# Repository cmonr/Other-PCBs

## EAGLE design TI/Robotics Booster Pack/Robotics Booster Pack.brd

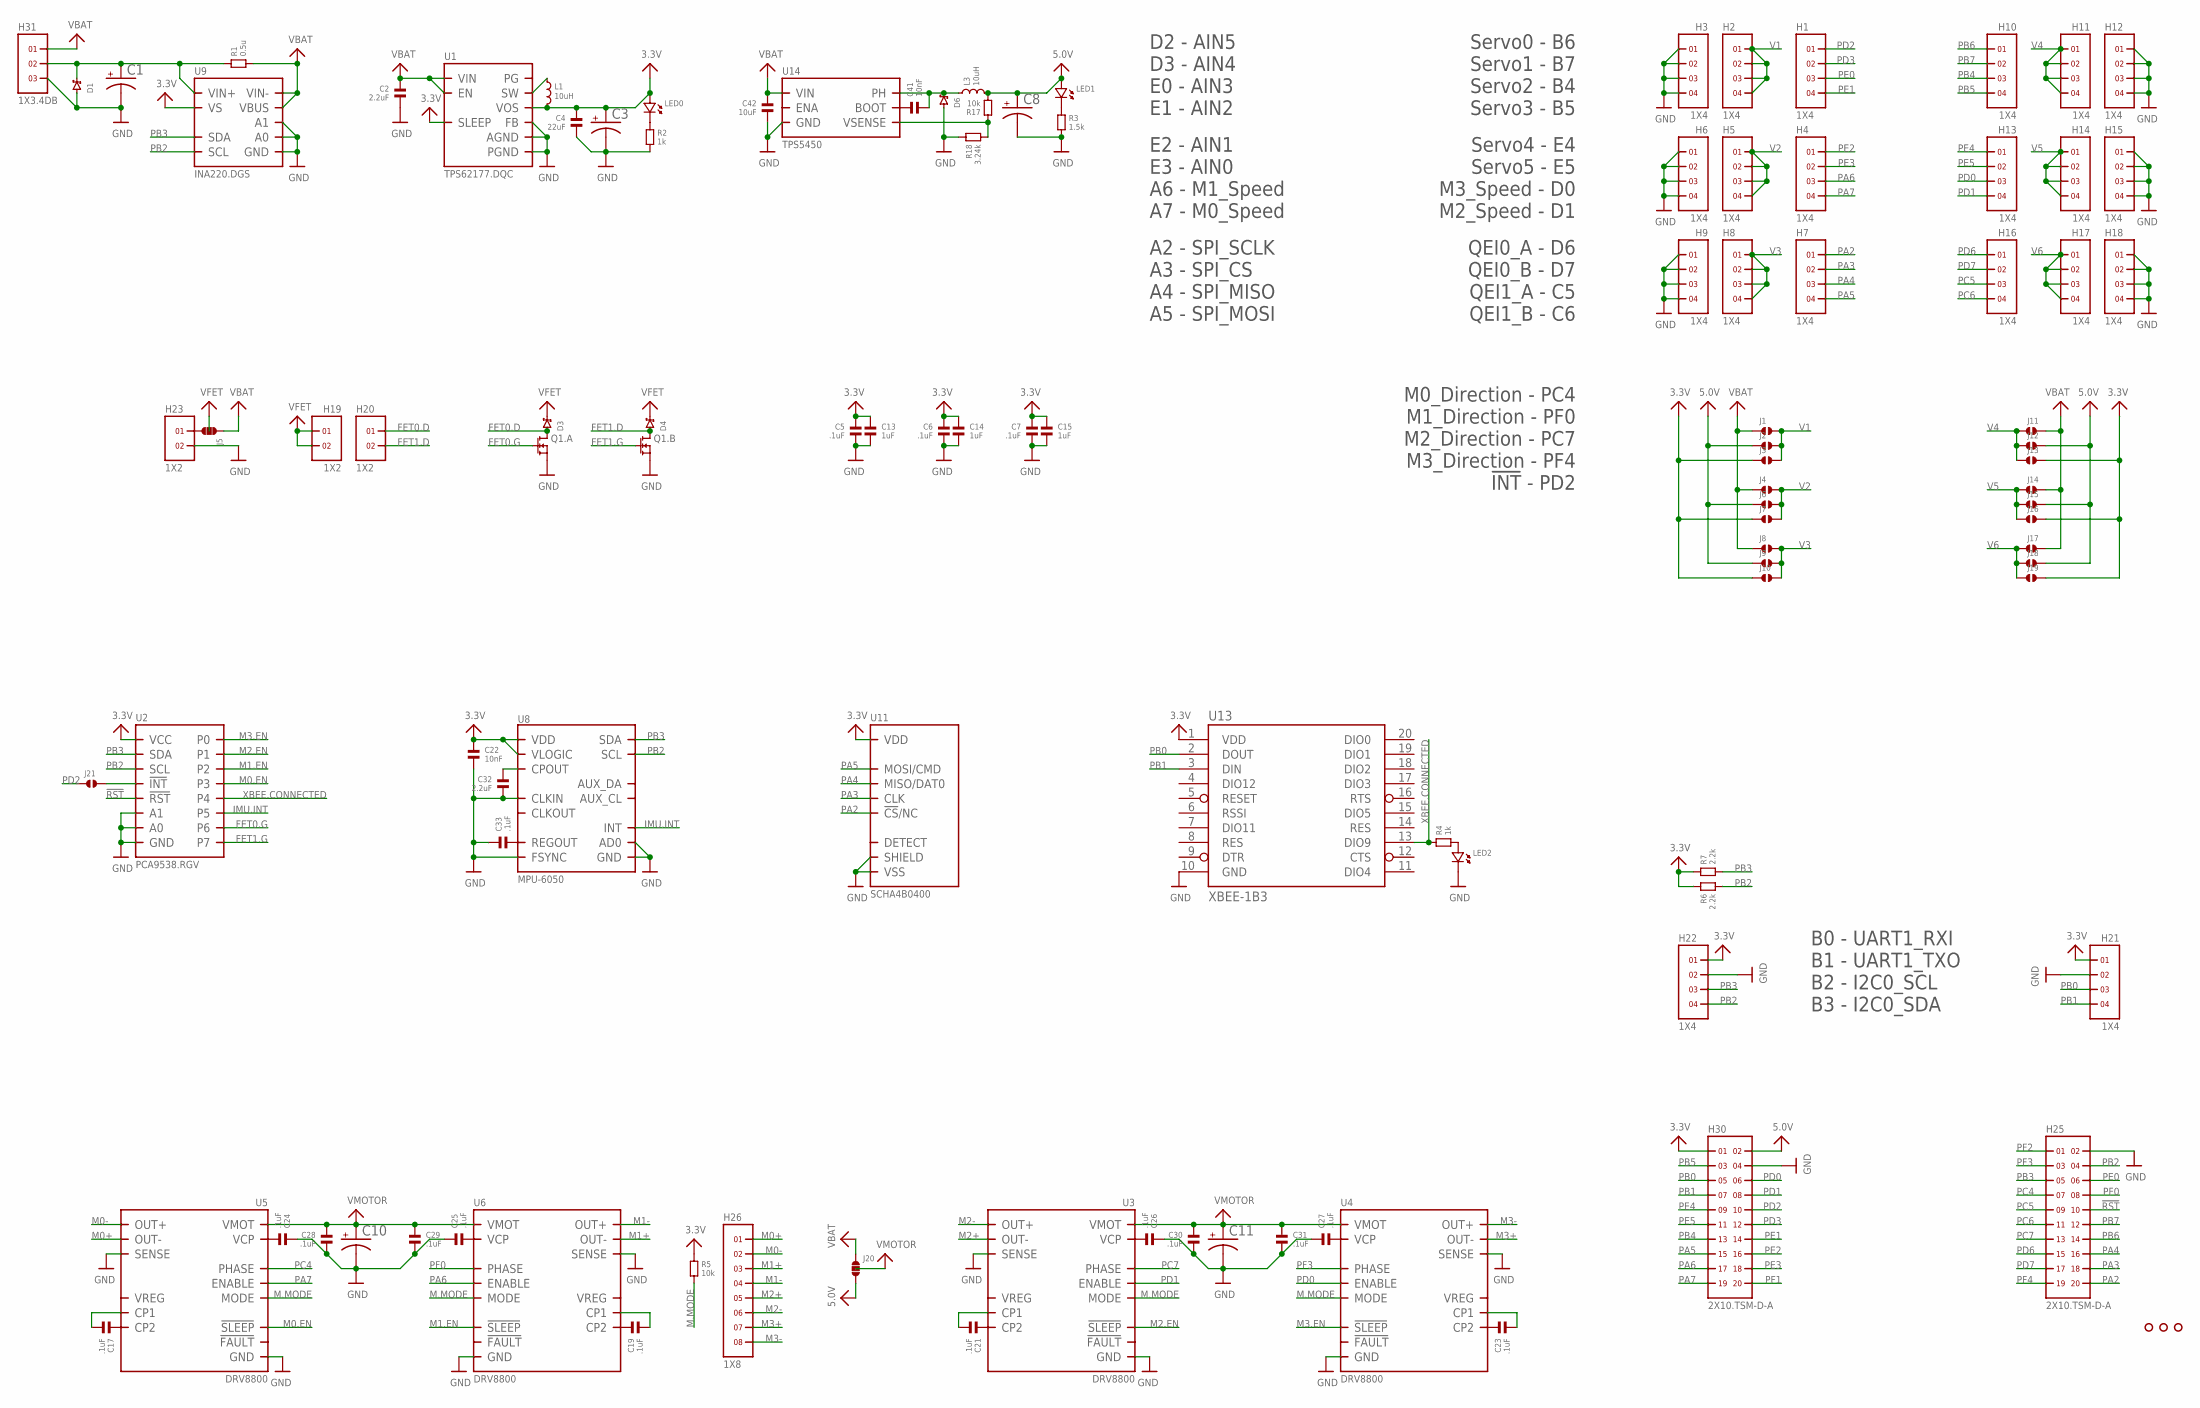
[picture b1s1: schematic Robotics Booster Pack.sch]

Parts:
C1, C3, C8, C10, C11: CPOL-USE; PANASONIC_E
C2, C32: 2.2uF; 0603
C4: 22uF; 0805
C5, C6, C7, C17, C19, C21, C23, C24, C25, C26, C27, C28, C29, C30, C31, C33: .1uF; 0603
C13, C14, C15: 1uF; 0603
C22, C41: 10nF; 0603
C42: 10uF; 1206
D1, D3, D4: CDBMT2100-HF; SOD-123H
D6: CDBC5XXX-G; DO-214AB
H1, H2, H3, H4, H5, H6, H7, H8, H9, H10, H11, H12, H13, H14, H15, H16, H17, H18, H21, H22: 1X4
H19, H20, H23: 1X2
H25, H30: 2X10.TSM-D-A; TSM-110-XX-XXX-DV-A
H26: 1X8; 1824480000
H31: 1X3.4DB; 4DB-P108-02
J1, J2, J4, J6, J8, J9, J11, J13, J14, J15, J17, J18, J21: SOLDERJUMPER.2.LRG; 2.LRG
J3, J7, J10, J12, J16, J19: SOLDERJUMPER.2.LRG.PASTE; 2.LRG.PASTE
J5, J20: SOLDERJUMPER.3.LRG.12; 3.LRG.12
L1: 10uH; SRN6045
L3: 10uH; XAL6060
LED0, LED1, LED2: LED.0603; 0603.LED
Q1: FDMA; MICROFET.2X2
R1: 0.5u; 2512
R2, R4: 1k; 0603
R3: 1.5k; 0603
R5, R17: 10k; 0603
R6, R7: 2.2k; 0603
R18: 3.24k; 0603
U1: TPS62177.DQC; DQC
U2: PCA9538.RGV; RGV.16
U3, U4, U5, U6: DRV8800; RTY.16
U8: MPU-6050; QFN.24.4X4
U9: INA220.DGS; DGS.10
U11: SCHA4B0400
U13: XBEE-1B3; XBEE-SMD
U14: TPS5450; DDA
U$3, U$4, U$21: HOLE.4MM; #4

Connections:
3.3V: C3.+, C4.1, C5.1, C6.1, C7.1, C13.1, C14.1, C15.1, C22.1, H21.1, H22.1, H30.1, J3.1, J7.1, J10.1, J13.1, J16.1, J19.1, L1.2, LED0.P$1 (1), R5.1, R6.1, R7.1, U1.8 (SLEEP), U1.10 (VOS), U2.14 (VCC), U8.8 (VLOGIC), U8.13 (VDD), U9.6 (VS), U11.VDD, U13.1 (VDD)
5.0V: C8.+, H30.2, J2.1, J6.1, J9.1, J12.1, J15.1, J18.1, J20.3, L3.2, LED1.P$1 (1), R17.2
!RST: H25.10, U2.1 (!RST)
FET0.D: D3.2, H20.1, Q1.6 (D), Q1.PAD@1 (D)
FET0.G: Q1.2 (G), U2.9 (P6)
FET1.D: D4.2, H20.2, Q1.3 (D), Q1.PAD@2 (D)
FET1.G: Q1.5 (G), U2.10 (P7)
GND: C1.-, C2.2, C3.-, C4.2, C5.2, C6.2, C7.2, C8.-, C10.-, C11.-, C13.2, C14.2, C15.2, C22.2, C24.1, C25.1, C26.1, C27.1, C28.2, C29.2, C30.2, C31.2, C32.2, C33.1, C42.2, D1.2, D6.2, H3.1, H3.2, H3.3, H3.4, H6.1, H6.2, H6.3, H6.4, H9.1, H9.2, H9.3, H9.4, H12.1, H12.2, H12.3, H12.4, H15.1, H15.2, H15.3, H15.4, H18.1, H18.2, H18.3, H18.4, H21.2, H22.2, H23.2, H25.2, H30.4, H31.3, LED2.P$2 (2), Q1.1 (S), Q1.4 (S), R2.2, R3.2, R18.1, U1.1 (PGND), U1.5 (FB), U1.6 (AGND), U1.PAD (PGND), U2.6 (GND), U2.15 (A0), U2.16 (A1), U2.PAD (GND), U3.2 (GND), U3.7 (SENSE), U3.12 (GND), U3.PAD (GND), U4.2 (GND), U4.7 (SENSE), U4.12 (GND), U4.PAD (GND), U5.2 (GND), U5.7 (SENSE), U5.12 (GND), U5.PAD (GND), U6.2 (GND), U6.7 (SENSE), U6.12 (GND), U6.PAD (GND), U8.1 (CLKIN), U8.9 (AD0), U8.11 (FSYNC), U8.18 (GND), U9.1 (A1), U9.2 (A0), U9.7 (GND), U11.GND (VSS), U11.GND@1 (VSS), U11.GND@2 (VSS), U11.SHIELD, U11.SHIELD@1 (SHIELD), U11.SHIELD@2 (SHIELD), U11.SHIELD@3 (SHIELD), U11.VSS, U13.10 (GND), U14.6 (GND), U14.PAD (GND)
IMU.INT: U2.8 (P5), U8.12 (INT)
M0+: H26.1@1 (1), H26.1@2 (1), U5.9 (OUT-)
M0-: H26.2@1 (2), H26.2@2 (2), U5.6 (OUT+)
M0.EN: U2.5 (P3), U5.3 (!SLEEP)
M1+: H26.3@1 (3), H26.3@2 (3), U6.9 (OUT-)
M1-: H26.4@1 (4), H26.4@2 (4), U6.6 (OUT+)
M1.EN: U2.4 (P2), U6.3 (!SLEEP)
M2+: H26.5@1 (5), H26.5@2 (5), U3.9 (OUT-)
M2-: H26.6@1 (6), H26.6@2 (6), U3.6 (OUT+)
M2.EN: U2.3 (P1), U3.3 (!SLEEP)
M3+: H26.7@1 (7), H26.7@2 (7), U4.9 (OUT-)
M3-: H26.8@1 (8), H26.8@2 (8), U4.6 (OUT+)
M3.EN: U2.2 (P0), U4.3 (!SLEEP)
M.MODE: R5.2, U3.16 (MODE), U4.16 (MODE), U5.16 (MODE), U6.16 (MODE)
unnamed: L1.1, U1.9 (SW)
unnamed: LED0.P$2 (2), R2.1
unnamed: LED1.P$2 (2), R3.1
unnamed: LED2.P$1 (1), R4.2
unnamed: H23.1, J5.3
unnamed: C33.2, U8.10 (REGOUT)
unnamed: J21.2, U2.11 (!INT)
unnamed: C17.1, U5.11 (CP2)
unnamed: C24.2, U5.13 (VCP)
unnamed: C25.2, U6.13 (VCP)
unnamed: C26.2, U3.13 (VCP)
unnamed: C27.2, U4.13 (VCP)
unnamed: C1.+, D1.1, H31.2, R1.1, U9.10 (VIN+)
unnamed: C32.1, U8.20 (CPOUT)
unnamed: C19.1, U6.11 (CP2)
unnamed: C21.1, U3.11 (CP2)
unnamed: C23.1, U4.11 (CP2)
unnamed: C41.1, U14.1 (BOOT)
unnamed: C41.2, D6.1, L3.1, U14.8 (PH)
unnamed: R17.1, R18.2, U14.4 (VSENSE)
unnamed: C21.2, U3.10 (CP1)
unnamed: C17.2, U5.10 (CP1)
unnamed: C19.2, U6.10 (CP1)
unnamed: C23.2, U4.10 (CP1)
PA2: H7.1, H25.20, U11.!CS!/NC/DAT3 (!CS!/NC)
PA3: H7.2, H25.18, U11.CLK
PA4: H7.3, H25.16, U11.MISO/DAT0
PA5: H7.4, H30.15, U11.MOSI/CMD
PA6: H4.3, H30.17, U6.4 (ENABLE)
PA7: H4.4, H30.19, U5.4 (ENABLE)
PB0: H21.3, H30.5, U13.2 (DOUT)
PB1: H21.4, H30.7, U13.3 (DIN)
PB2: H22.4, H25.4, R6.2, U2.12 (SCL), U8.23 (SCL), U9.5 (SCL)
PB3: H22.3, H25.5, R7.2, U2.13 (SDA), U8.24 (SDA), U9.4 (SDA)
PB4: H10.3, H30.13
PB5: H10.4, H30.3
PB6: H10.1, H25.14
PB7: H10.2, H25.12
PC4: H25.7, U5.1 (PHASE)
PC5: H16.3, H25.9
PC6: H16.4, H25.11
PC7: H25.13, U3.1 (PHASE)
PD0: H13.3, H30.6, U4.4 (ENABLE)
PD1: H13.4, H30.8, U3.4 (ENABLE)
PD2: H1.1, H30.10, J21.1
PD3: H1.2, H30.12
PD6: H16.1, H25.15
PD7: H16.2, H25.17
PE0: H1.3, H25.6
PE1: H1.4, H30.14
PE2: H4.1, H30.16
PE3: H4.2, H30.18
PE4: H13.1, H30.9
PE5: H13.2, H30.11
PF0: H25.8, U6.1 (PHASE)
PF1: H30.20
PF2: H25.1
PF3: H25.3, U4.1 (PHASE)
PF4: H25.19
V1: H2.1, H2.2, H2.3, H2.4, J1.2, J2.2, J3.2
V2: H5.1, H5.2, H5.3, H5.4, J4.2, J6.2, J7.2
V3: H8.1, H8.2, H8.3, H8.4, J8.2, J9.2, J10.2
V4: H11.1, H11.2, H11.3, H11.4, J11.2, J12.2, J13.2
V5: H14.1, H14.2, H14.3, H14.4, J14.2, J15.2, J16.2
V6: H17.1, H17.2, H17.3, H17.4, J17.2, J18.2, J19.2
VBAT: C2.1, C42.1, H31.1, J1.1, J4.1, J5.1, J8.1, J11.1, J14.1, J17.1, J20.1, R1.2, U1.2 (VIN), U1.3 (EN), U9.8 (VBUS), U9.9 (VIN-), U14.7 (VIN)
VFET: D3.1, D4.1, H19.1, H19.2, J5.2
VMOTOR: C10.+, C11.+, C28.1, C29.1, C30.1, C31.1, J20.2, U3.8 (VMOT), U4.8 (VMOT), U5.8 (VMOT), U6.8 (VMOT)
XBEE.CONNECTED: R4.1, U2.7 (P4), U13.13 (DIO9)

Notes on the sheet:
D2 - AIN5 D3 - AIN4 E0 - AIN3 E1 - AIN2
E2 - AIN1 E3 - AIN0 A6 - M1_Speed A7 - M0_Speed
A2 - SPI_SCLK A3 - SPI_CS A4 - SPI_MISO A5 - SPI_MOSI
Servo0 - B6 Servo1 - B7 Servo2 - B4 Servo3 - B5
Servo4 - E4 Servo5 - E5 M3_Speed - D0 M2_Speed - D1
QEI0_A - D6 QEI0_B - D7 QEI1_A - C5 QEI1_B - C6
B0 - UART1_RXI B1 - UART1_TXO B2 - I2C0_SCL B3 - I2C0_SDA
M0_Direction - PC4 M1_Direction - PF0 M2_Direction - PC7 M3_Direction - PF4 !INT! - PD2

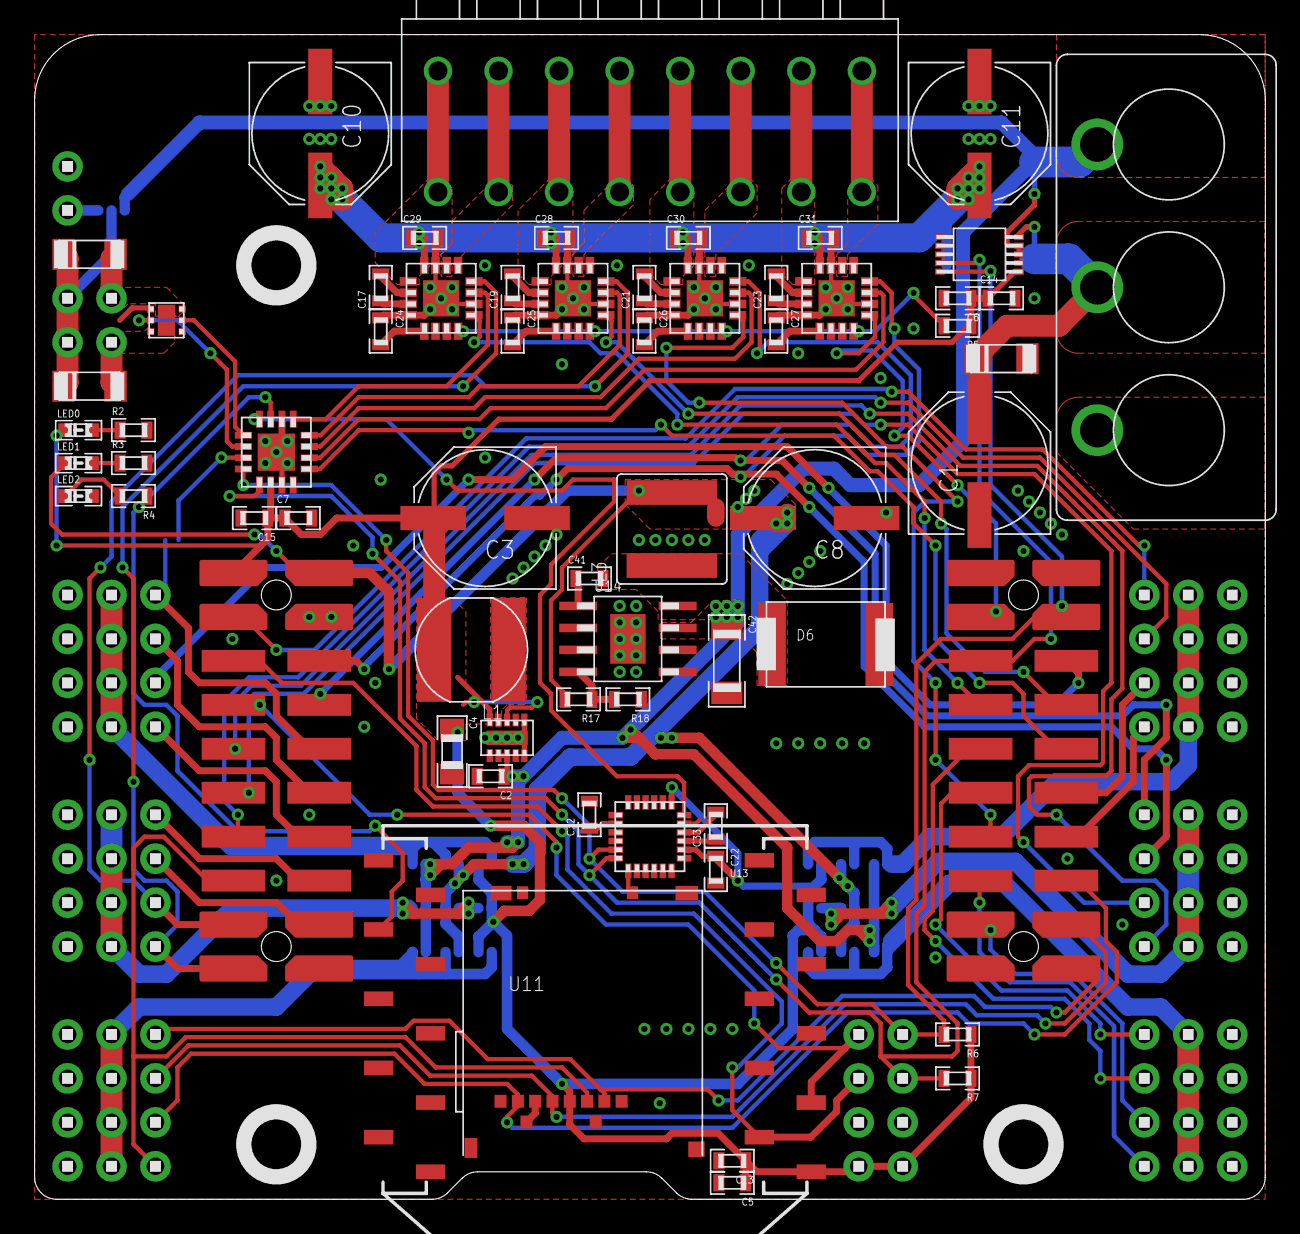
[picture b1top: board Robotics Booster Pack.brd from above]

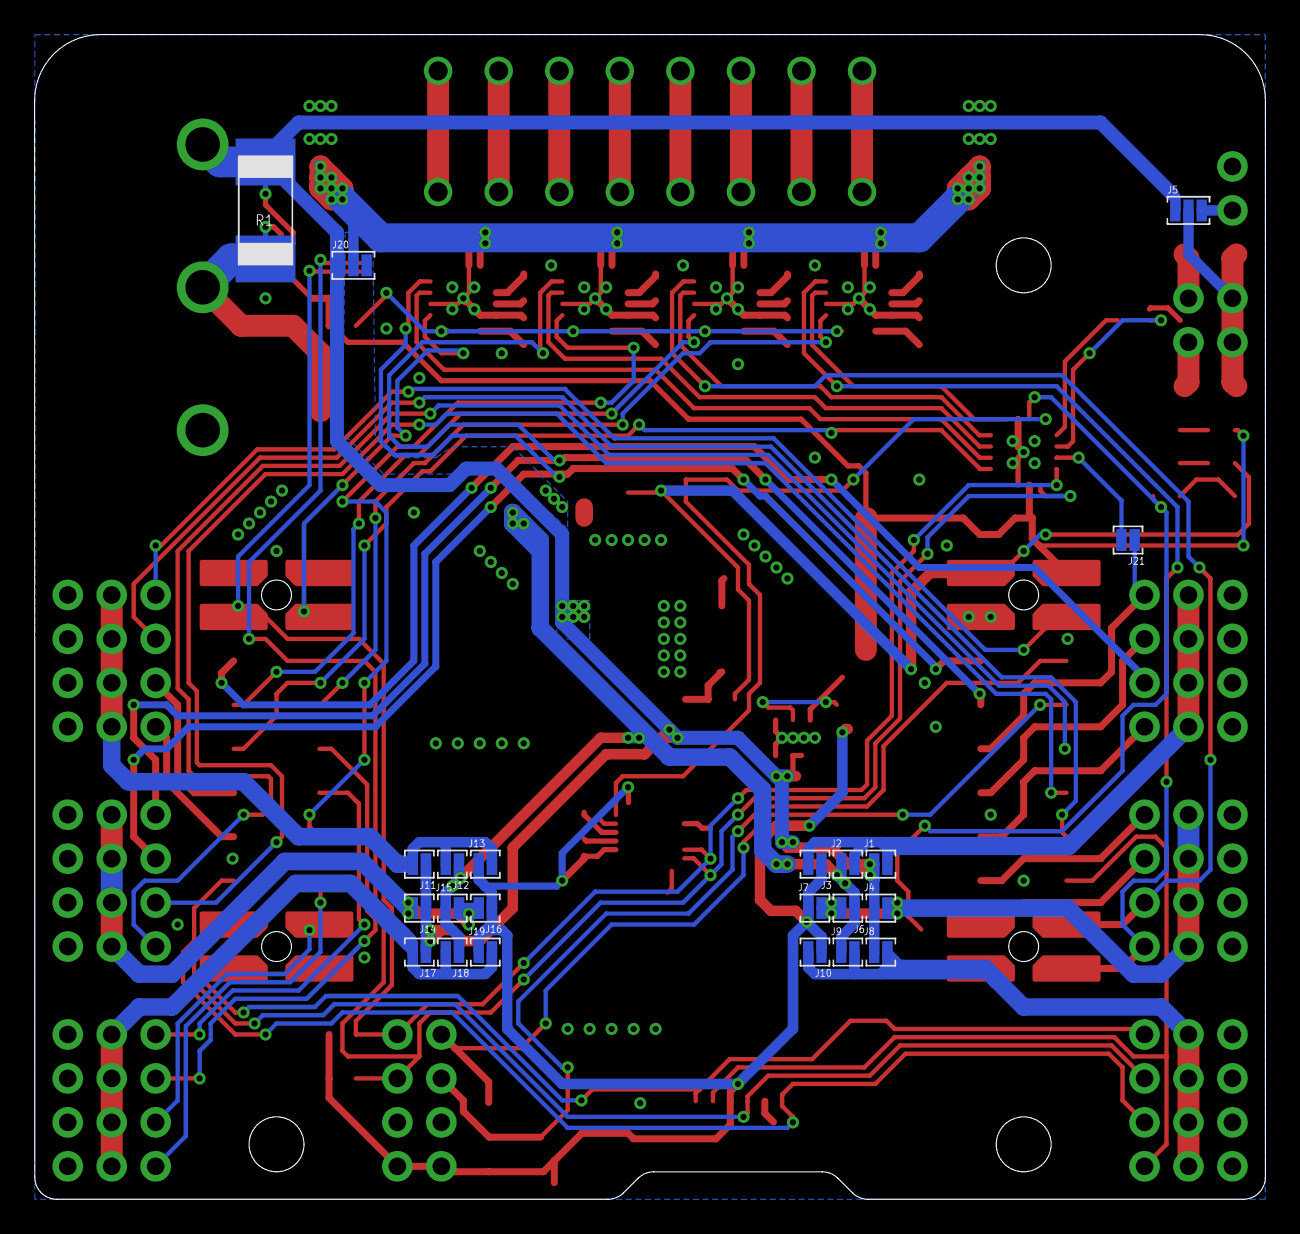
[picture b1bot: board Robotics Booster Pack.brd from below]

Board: 2 copper layers, 71.1 x 67.3 mm, 111 parts (22 on the bottom side), 88 nets.

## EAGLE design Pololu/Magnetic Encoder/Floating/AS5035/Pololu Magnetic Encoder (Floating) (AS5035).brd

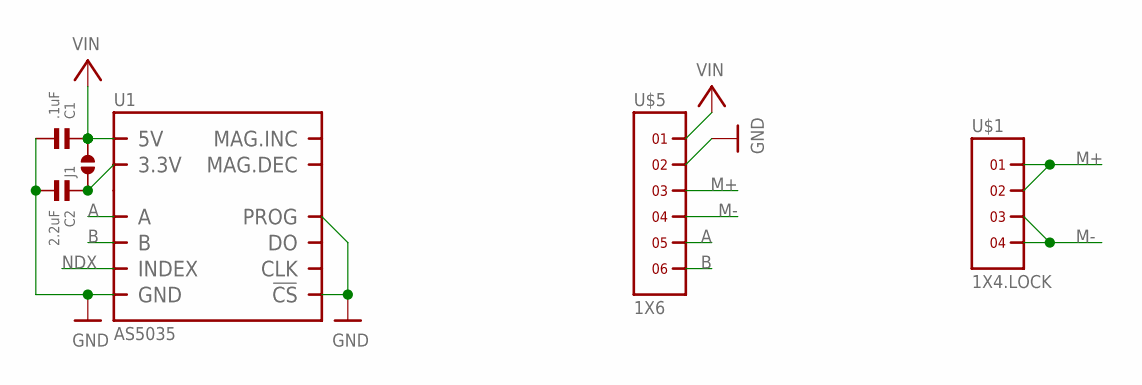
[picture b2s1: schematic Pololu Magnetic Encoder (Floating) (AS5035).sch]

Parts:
C1: .1uF; 0603
C2: 2.2uF; 0603
J1: SOLDERJUMPER.2.LRG.PASTE; 2.LRG.PASTE
U1: AS5035; SSOP16
U$1: 1X4.LOCK
U$5: 1X6

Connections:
A: U1.3 (A), U$5.5
B: U1.4 (B), U$5.6
GND: C1.2, C2.2, U1.7 (GND), U1.8 (PROG), U1.11 (!CS), U$5.2
M+: U$1.1, U$1.2, U$5.3
M-: U$1.3, U$1.4, U$5.4
unnamed: C2.1, J1.1, U1.15 (3.3V)
NDX: U1.6 (INDEX)
VIN: C1.1, J1.2, U1.16 (5V), U$5.1

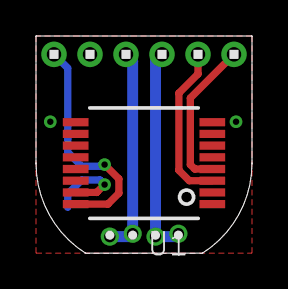
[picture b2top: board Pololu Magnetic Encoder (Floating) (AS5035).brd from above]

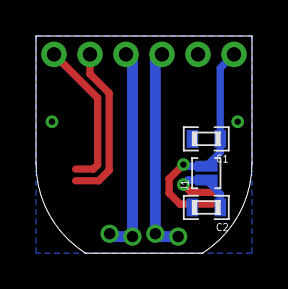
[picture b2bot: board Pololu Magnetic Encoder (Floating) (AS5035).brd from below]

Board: 2 copper layers, 12.0 x 12.1 mm, 6 parts (3 on the bottom side), 7 nets.

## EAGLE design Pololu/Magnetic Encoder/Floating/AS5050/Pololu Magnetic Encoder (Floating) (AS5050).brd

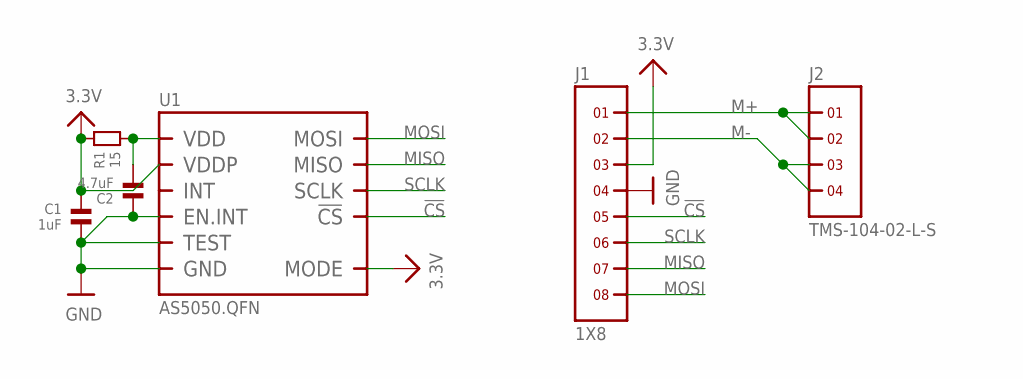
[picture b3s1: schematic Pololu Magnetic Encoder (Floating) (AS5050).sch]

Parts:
C1: 1uF; 0603
C2: 4.7uF; 0603
J1: 1X8
J2: TMS-104-02-L-S; 1X4.LOCK
R1: 15; 0603
U1: AS5050.QFN; QFN.16

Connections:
3.3V: C1.1, J1.3, R1.1, U1.11 (VDDP), U1.14 (MODE)
!CS: J1.5, U1.4 (!CS)
GND: C1.2, C2.1, J1.4, U1.9 (TEST), U1.10 (EN.INT), U1.13 (GND)
M+: J1.1, J2.1, J2.2
M-: J1.2, J2.3, J2.4
MISO: J1.7, U1.2 (MISO)
MOSI: J1.8, U1.1 (MOSI)
unnamed: C2.2, R1.2, U1.12 (VDD)
SCLK: J1.6, U1.3 (SCLK)

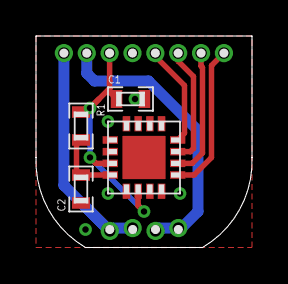
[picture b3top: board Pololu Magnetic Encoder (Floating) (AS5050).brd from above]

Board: 2 copper layers, 12.0 x 11.8 mm, 6 parts (0 on the bottom side), 9 nets.

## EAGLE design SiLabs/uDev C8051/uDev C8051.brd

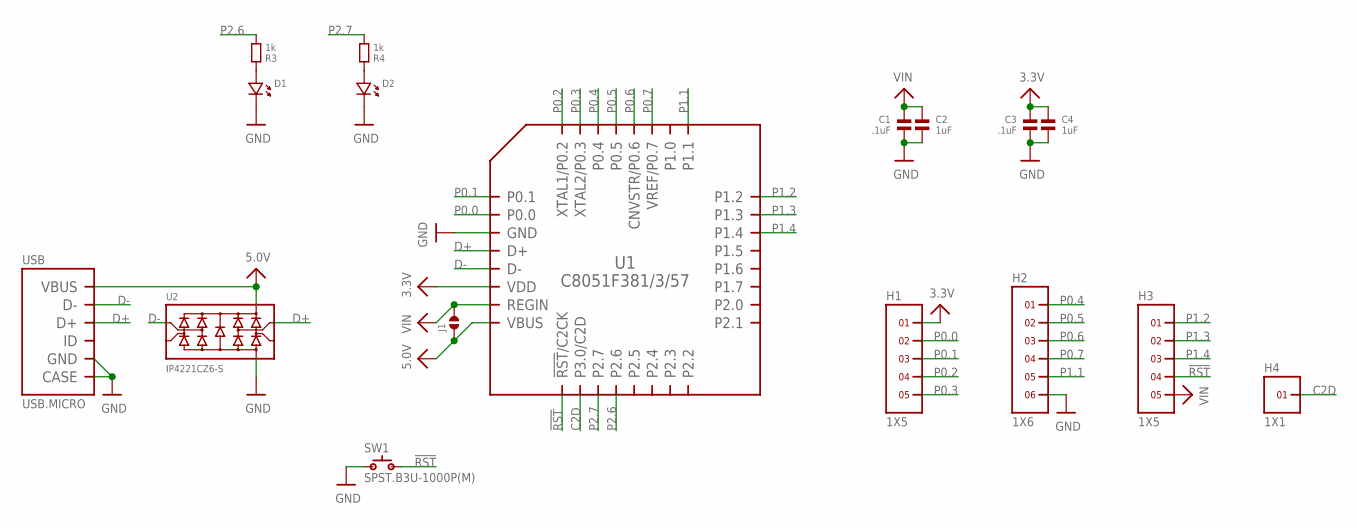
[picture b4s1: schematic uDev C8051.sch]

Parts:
C1, C3: .1uF; 0402
C2, C4: 1uF; 0402
D1, D2: LED.0402; 0402.LED
H1, H3: 1X5
H2: 1X6
H4: 1X1
J1: SOLDERJUMPER.2.SML; 2.SML
R3, R4: 1k; 0402
SW1: SPST.B3U-1000P(M); B3U-1000P(M)
U1: C8051F381/3/57; QFN32
U2: IP4221CZ6-S; DFN1410-6
USB: USB.MICRO; 1554266-1

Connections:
3.3V: C3.1, C4.1, H1.1, U1.6 (VDD)
5.0V: J1.1, U1.8 (VBUS), U2.5, USB.1 (VBUS)
!RST: H3.4, SW1.2, U1.9 (!RST!/C2CK)
C2D: H4.1, U1.10 (P3.0/C2D)
D+: U1.4 (D+), U2.3, USB.3 (D+)
D-: U1.5 (D-), U2.1, USB.2 (D-)
GND: C1.2, C2.2, C3.2, C4.2, D1.P$2 (2), D2.P$2 (2), H2.6, SW1.1, U1.3 (GND), U1.PAD (GND), U2.2, USB.5 (GND), USB.PAD1@1 (CASE), USB.PAD1@2 (CASE), USB.PAD1@VIA1 (CASE), USB.PAD1@VIA2 (CASE), USB.PAD1@VIA3 (CASE), USB.PAD1@VIA4 (CASE), USB.PAD1@VIA5 (CASE), USB.PAD2 (CASE), USB.PAD2@VIA1 (CASE), USB.PAD2@VIA2 (CASE), USB.PAD2@VIA3 (CASE), USB.PAD2@VIA4 (CASE), USB.PAD2@VIA5 (CASE), USB.PAD2@VIA6 (CASE), USB.PAD2@VIA7 (CASE), USB.PAD3 (CASE), USB.PAD3@VIA1 (CASE), USB.PAD3@VIA2 (CASE), USB.PAD3@VIA3 (CASE), USB.PAD3@VIA4 (CASE), USB.PAD3@VIA5 (CASE), USB.PAD3@VIA6 (CASE), USB.PAD3@VIA7 (CASE), USB.PAD4@1 (CASE), USB.PAD4@2 (CASE), USB.PAD4@VIA1 (CASE), USB.PAD4@VIA2 (CASE), USB.PAD4@VIA3 (CASE), USB.PAD4@VIA4 (CASE), USB.PAD4@VIA5 (CASE)
unnamed: D1.P$1 (1), R3.1
unnamed: D2.P$1 (1), R4.1
P0.0: H1.2, U1.2 (P0.0)
P0.1: H1.3, U1.1 (P0.1)
P0.2: H1.4, U1.32 (XTAL1/P0.2)
P0.3: H1.5, U1.31 (XTAL2/P0.3)
P0.4: H2.1, U1.30 (P0.4)
P0.5: H2.2, U1.29 (P0.5)
P0.6: H2.3, U1.28 (CNVSTR/P0.6)
P0.7: H2.4, U1.27 (VREF/P0.7)
P1.1: H2.5, U1.25 (P1.1)
P1.2: H3.1, U1.24 (P1.2)
P1.3: H3.2, U1.23 (P1.3)
P1.4: H3.3, U1.22 (P1.4)
P2.6: R3.2, U1.12 (P2.6)
P2.7: R4.2, U1.11 (P2.7)
VIN: C1.1, C2.1, H3.5, J1.2, U1.7 (REGIN)

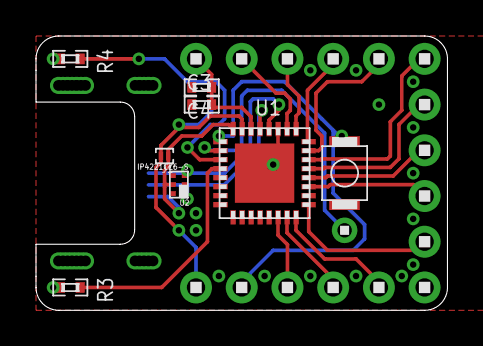
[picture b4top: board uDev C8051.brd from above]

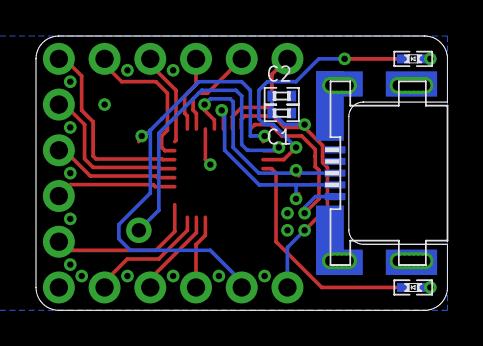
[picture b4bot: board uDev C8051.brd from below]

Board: 2 copper layers, 22.9 x 15.2 mm, 17 parts (5 on the bottom side), 24 nets.

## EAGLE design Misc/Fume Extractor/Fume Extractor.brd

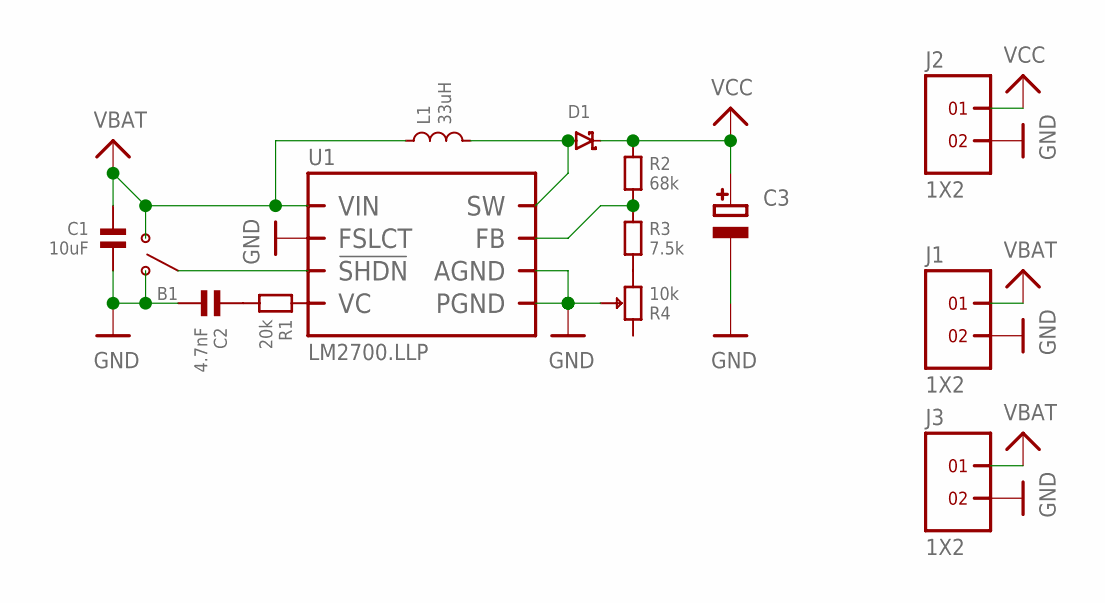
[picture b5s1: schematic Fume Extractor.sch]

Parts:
B1: SSSS810701
C1: 10uF; 0805
C2: 4.7nF; 0603
C3: CAP_ELECTROLYTICPANASONIC_D; PANASONIC_D
D1: DIODE[SCHOTKY]-SOD123W; SOD123W
J1, J2, J3: 1X2
L1: 33uH; SRN6045
R1: 20k; 0603
R2: 68k; 0603
R3: 7.5k; 0603
R4: 10k; RS08U111Z001
U1: LM2700.LLP; LLP-EP

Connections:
GND: B1.3 (A), C1.2, C2.2, C3.-, J1.2, J2.2, J3.2, R4.B, U1.4 (AGND), U1.5 (PGND), U1.6 (PGND), U1.7 (PGND), U1.13 (FSLCT), U1.PAD (PGND)
unnamed: R2.2, R3.1, U1.2 (FB)
unnamed: C2.1, R1.2
unnamed: R3.2, R4.C
unnamed: D1.P$1 (1), L1.2, U1.8 (SW), U1.9 (SW), U1.10 (SW)
unnamed: B1.2 (COM), U1.3 (!SHDN)
unnamed: R1.1, U1.1 (VC)
VBAT: B1.1 (B), C1.1, J1.1, J3.1, L1.1, U1.12 (VIN)
VCC: C3.+, D1.P$2 (2), J2.1, R2.1

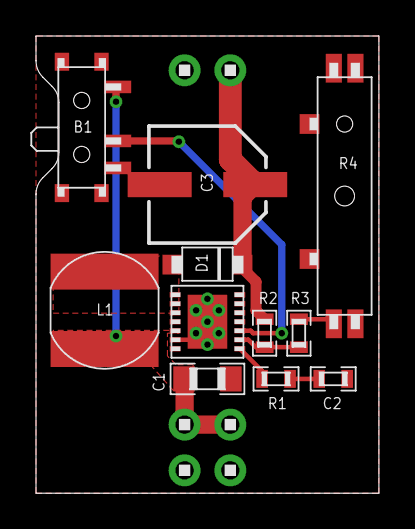
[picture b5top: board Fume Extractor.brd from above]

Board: 2 copper layers, 19.1 x 25.4 mm, 14 parts (0 on the bottom side), 9 nets.

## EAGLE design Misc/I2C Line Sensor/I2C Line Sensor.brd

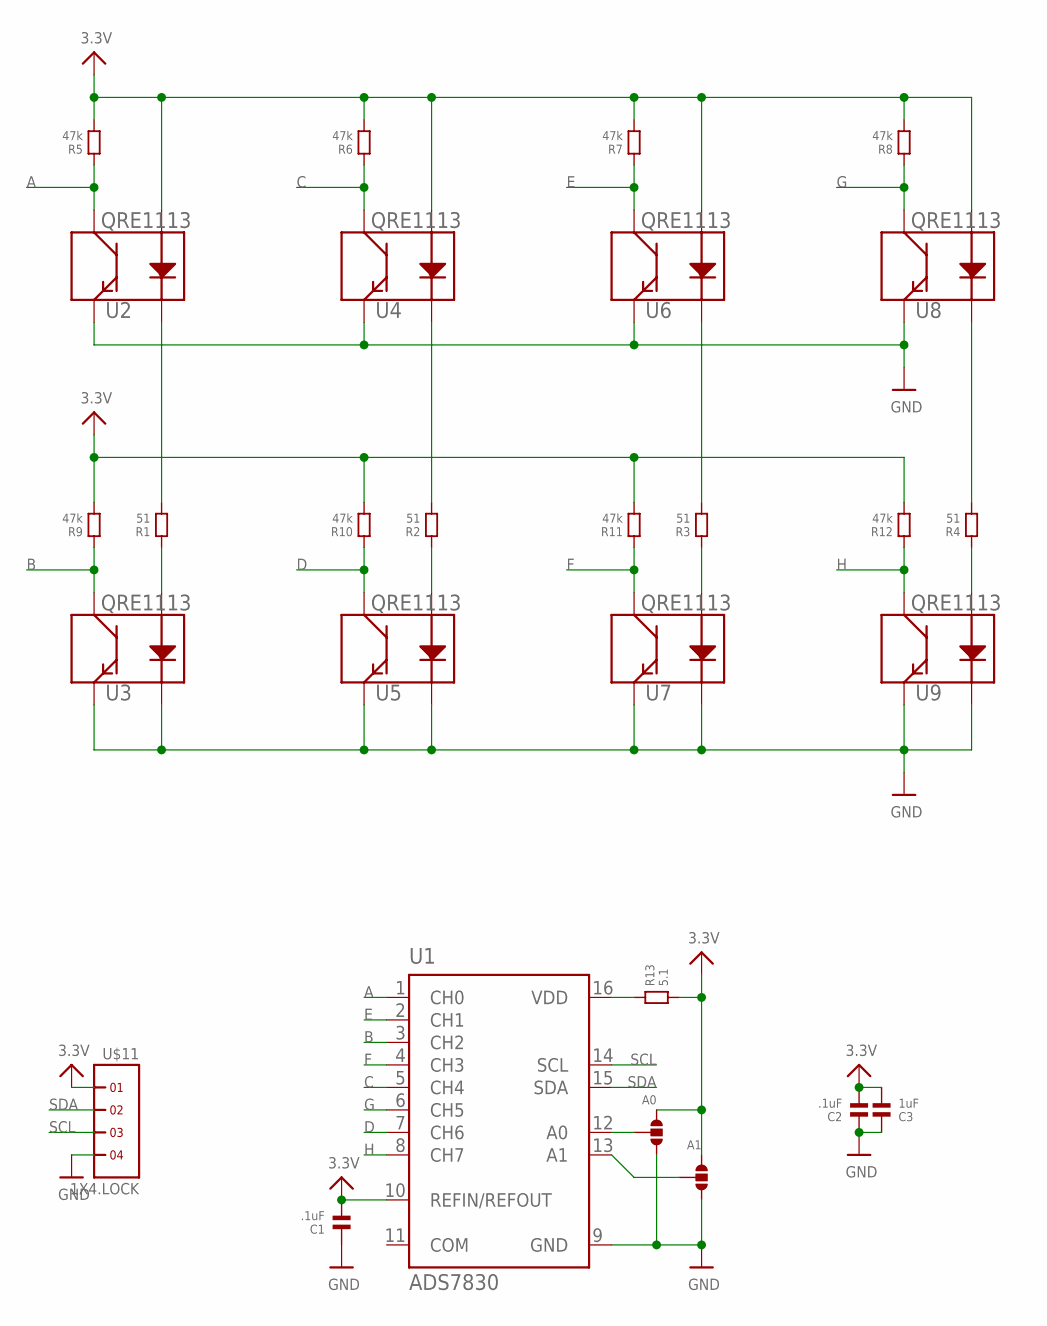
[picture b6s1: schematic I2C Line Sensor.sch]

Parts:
A0, A1: SOLDERJUMPER.3.LRG.23; 3.LRG.23
C1, C2: .1uF; 0603
C3: 1uF; 0603
R1, R2, R3, R4: 51; 0603
R5, R6, R7, R8, R9, R10, R11, R12: 47k; 0603
R13: 5.1; 0603
U1: ADS7830; TSSOP16-PW
U2, U3, U4, U5, U6, U7, U8, U9: QRE1113
U$11: 1X4.LOCK

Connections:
3.3V: A0.1, A1.1, C1.2, C2.2, C3.2, R5.2, R6.2, R7.2, R8.2, R9.2, R10.2, R11.2, R12.2, R13.2, U1.10 (REFIN/REFOUT), U2.1 (A), U4.1 (A), U6.1 (A), U8.1 (A), U$11.1
A: R5.1, U1.1 (CH0), U2.3 (C)
B: R9.1, U1.3 (CH2), U3.3 (C)
C: R6.1, U1.5 (CH4), U4.3 (C)
D: R10.1, U1.7 (CH6), U5.3 (C)
E: R7.1, U1.2 (CH1), U6.3 (C)
F: R11.1, U1.4 (CH3), U7.3 (C)
G: R8.1, U1.6 (CH5), U8.3 (C)
GND: A0.3, A1.3, C1.1, C2.1, C3.1, U1.9 (GND), U2.4 (E), U3.2 (K), U3.4 (E), U4.4 (E), U5.2 (K), U5.4 (E), U6.4 (E), U7.2 (K), U7.4 (E), U8.4 (E), U9.2 (K), U9.4 (E), U$11.4
H: R12.1, U1.8 (CH7), U9.3 (C)
unnamed: A0.2, U1.12 (A0)
unnamed: R1.2, U2.2 (K)
unnamed: R1.1, U3.1 (A)
unnamed: R2.1, U5.1 (A)
unnamed: R2.2, U4.2 (K)
unnamed: R3.2, U6.2 (K)
unnamed: R3.1, U7.1 (A)
unnamed: R4.2, U8.2 (K)
unnamed: R4.1, U9.1 (A)
unnamed: A1.2, U1.13 (A1)
unnamed: R13.1, U1.16 (VDD)
SCL: U1.14 (SCL), U$11.3
SDA: U1.15 (SDA), U$11.2

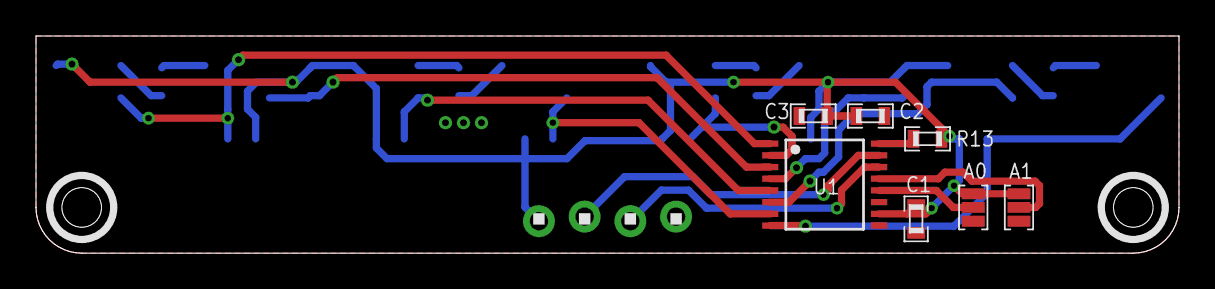
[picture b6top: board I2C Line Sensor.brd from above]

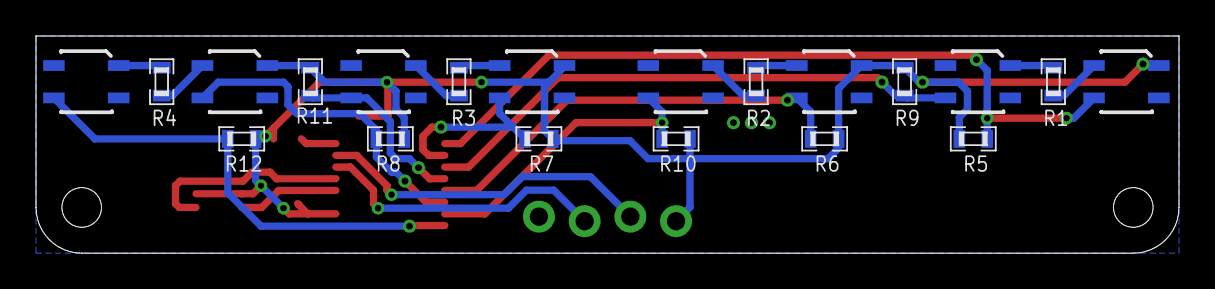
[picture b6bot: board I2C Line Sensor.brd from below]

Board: 2 copper layers, 63.5 x 12.1 mm, 28 parts (20 on the bottom side), 23 nets.

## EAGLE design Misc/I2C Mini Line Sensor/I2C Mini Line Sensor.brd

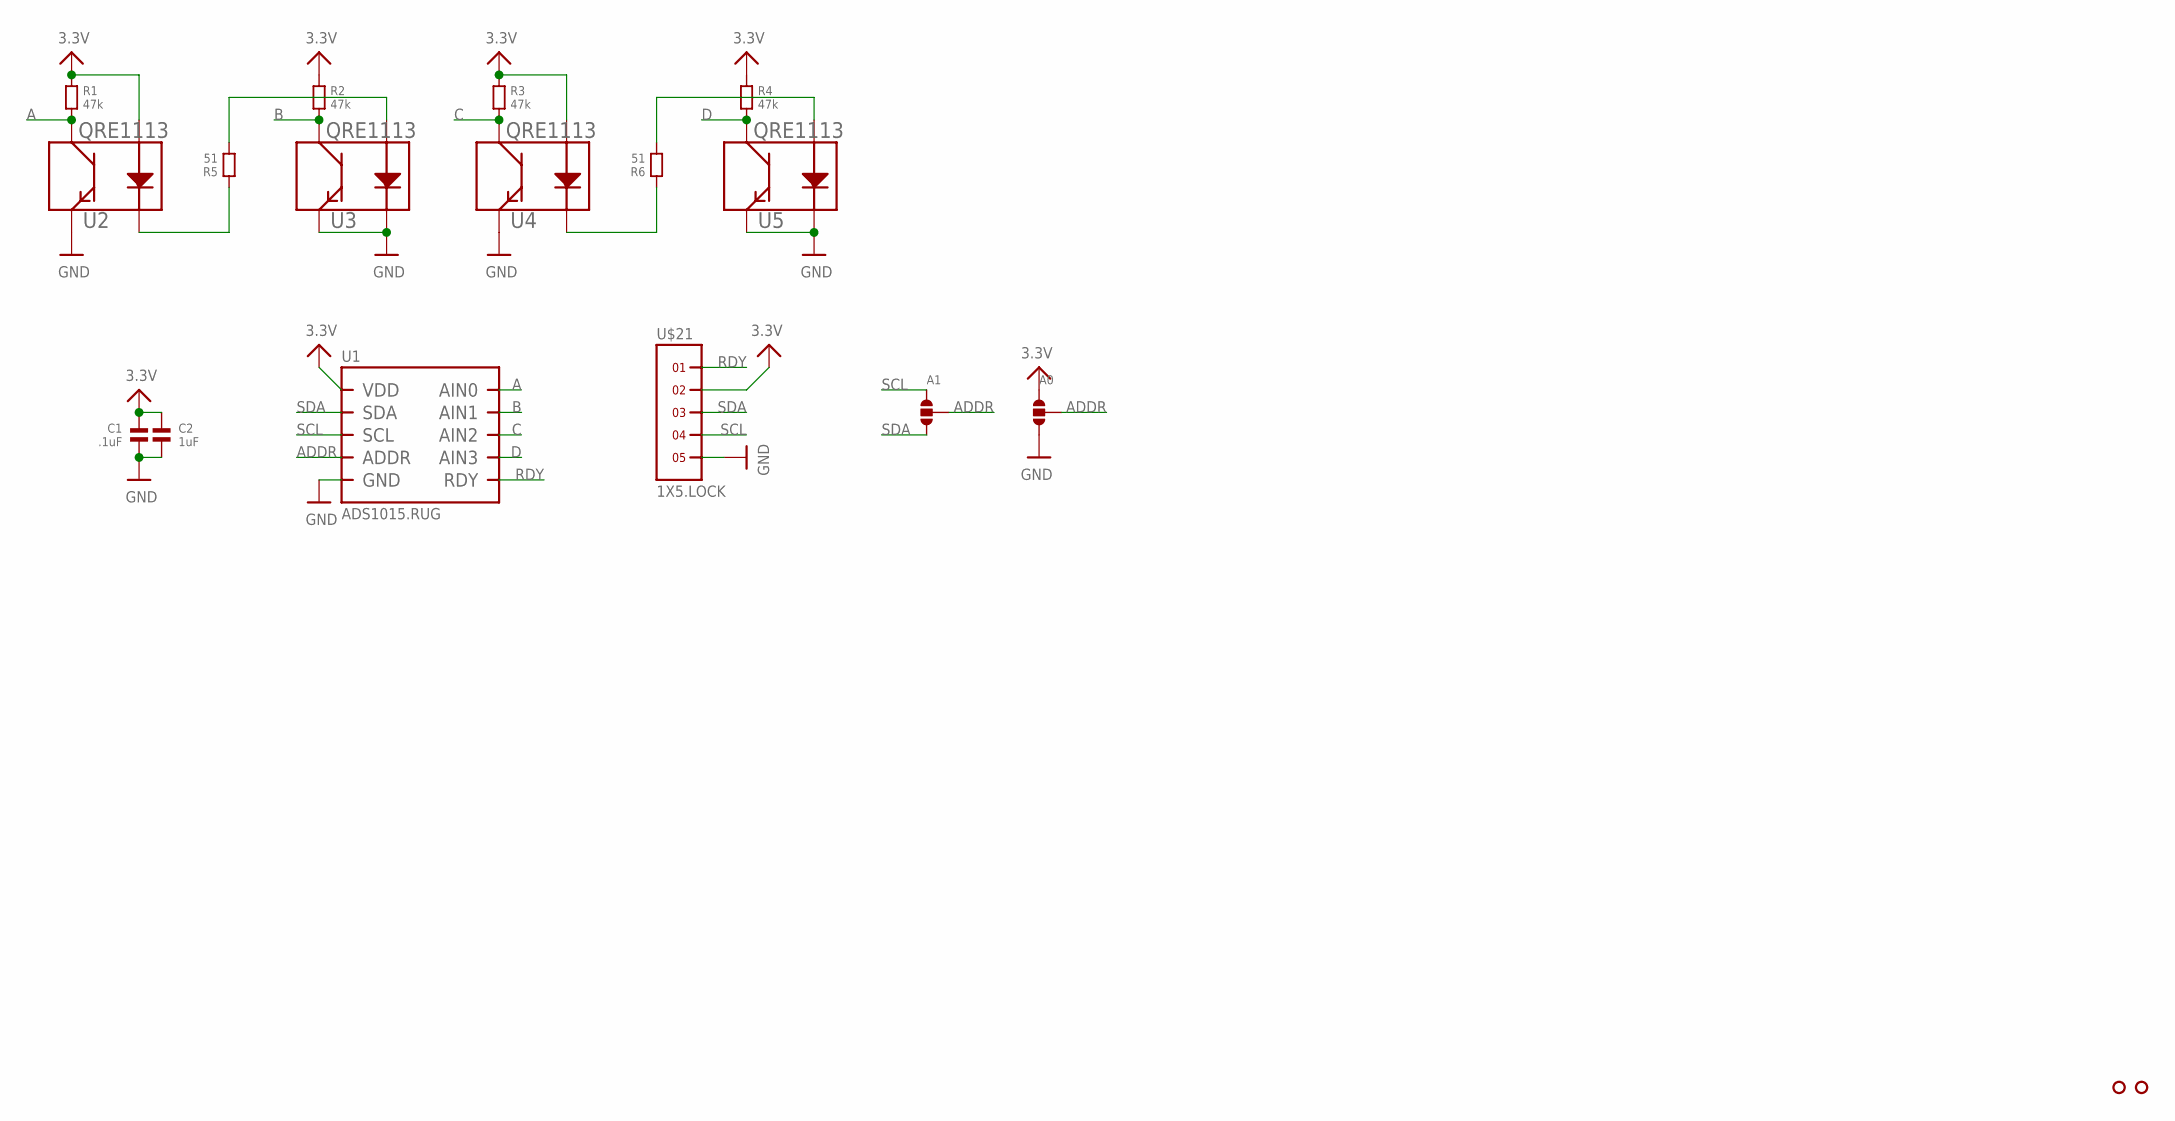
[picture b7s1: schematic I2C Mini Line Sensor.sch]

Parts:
A0, A1: SOLDERJUMPER.3.MED; 3.MED
C1: .1uF; 0603
C2: 1uF; 0603
R1, R2, R3, R4: 47k; 0603
R5, R6: 51; 0603
U1: ADS1015.RUG; RUG.10
U2, U3, U4, U5: QRE1113
U$3, U$18: HOLE.2MM; 2MM
U$21: 1X5.LOCK

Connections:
3.3V: A0.1, C1.1, C2.1, R1.1, R2.1, R3.1, R4.1, U1.8 (VDD), U2.1 (A), U4.1 (A), U$21.2
A: R1.2, U1.4 (AIN0), U2.3 (C)
ADDR: A0.2, A1.2, U1.1 (ADDR)
B: R2.2, U1.5 (AIN1), U3.3 (C)
C: R3.2, U1.6 (AIN2), U4.3 (C)
D: R4.2, U1.7 (AIN3), U5.3 (C)
GND: A0.3, C1.2, C2.2, U1.3 (GND), U2.4 (E), U3.2 (K), U3.4 (E), U4.4 (E), U5.2 (K), U5.4 (E), U$21.5
unnamed: R5.1, U2.2 (K)
unnamed: R5.2, U3.1 (A)
unnamed: R6.1, U4.2 (K)
unnamed: R6.2, U5.1 (A)
RDY: U1.2 (RDY), U$21.1
SCL: A1.1, U1.10 (SCL), U$21.4
SDA: A1.3, U1.9 (SDA), U$21.3

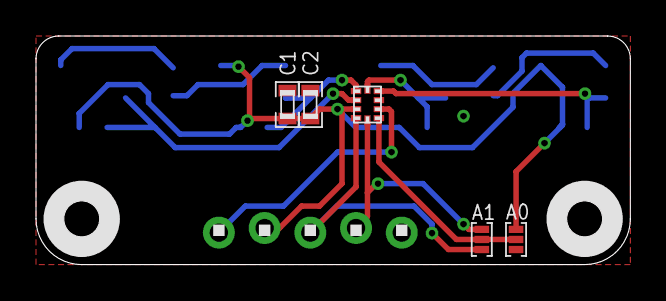
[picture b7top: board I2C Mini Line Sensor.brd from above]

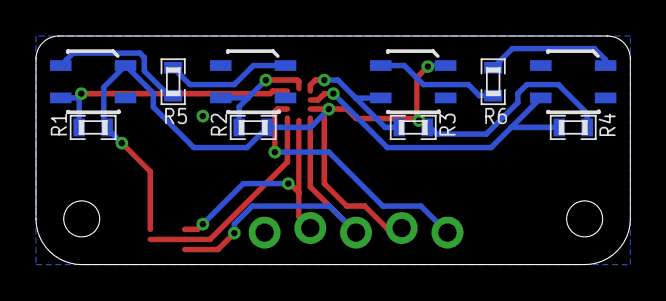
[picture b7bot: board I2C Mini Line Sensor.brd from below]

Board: 2 copper layers, 33.0 x 12.7 mm, 18 parts (10 on the bottom side), 14 nets.

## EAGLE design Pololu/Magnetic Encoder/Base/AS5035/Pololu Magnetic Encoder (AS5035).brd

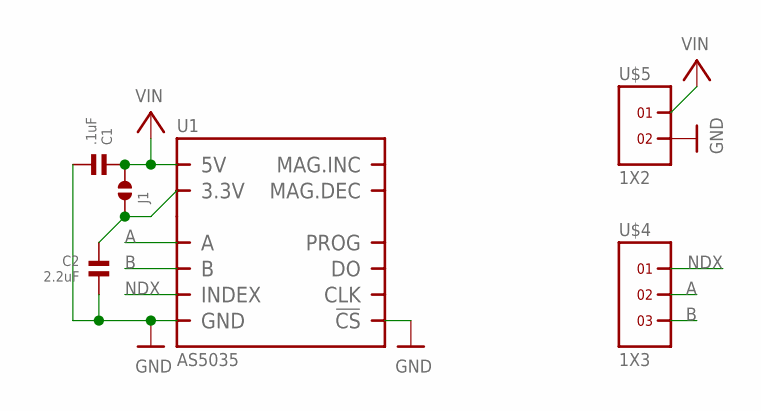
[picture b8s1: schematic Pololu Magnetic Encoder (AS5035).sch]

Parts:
C1: .1uF; 0603
C2: 2.2uF; 0603
J1: SOLDERJUMPER.2.LRG.PASTE; 2.LRG.PASTE
U1: AS5035; SSOP16
U$4: 1X3
U$5: 1X2

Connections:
A: U1.3 (A), U$4.2
B: U1.4 (B), U$4.3
GND: C1.2, C2.2, U1.7 (GND), U1.11 (!CS), U$5.2
unnamed: C2.1, J1.1, U1.15 (3.3V)
NDX: U1.6 (INDEX), U$4.1
VIN: C1.1, J1.2, U1.16 (5V), U$5.1

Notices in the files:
parts and their libraries:
microbuilder: This work is placed in the public domain, and may be freely used for commercial and non-commercial work with the following conditions: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
SparkFun-Sensors: Licensing: CC v3.0 Share-Alike You are welcome to use this library for commercial purposes.
